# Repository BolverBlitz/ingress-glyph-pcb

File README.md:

# Ingress Glyph PCB firmware

Ingress Glyph PCB firmware for controlling LED chains and managing device features.

## Hardware revisions

- Rev 1 drives the LED chain from GPIO2 and has a 4.5 W hardware limit.
- Rev 2 drives the LED chain from GPIO19 and uses GPIO5 (SDA) / GPIO6 (SCL)
  for two TMP117 temperature sensors. Its hardware limit is 8 W with dimming* applied as needed.
- Select the revision under **Settings → Hardware revision**. A revision change
  is saved and restarts the controller automatically.

*On Rev 2, the hotter TMP117 reading limits every LED mode. The configured power
is available up to 50 °C, then linearly derated to 0 W at 70 °C. The LEDs remain
off if either sensor is missing or has not produced a valid reading for five
seconds.

## Buttons

- Button 1: GPIO1, active-low with internal pull-up.
- Button 2: GPIO4, active-low with internal pull-up.
- Double-press Button 1: cycle Glyph Sequence, Random Glyphs, and Draw. The new
  mode is saved after 10 seconds without further button input.
- Hold Button 1 for 2 seconds: toggle Flashlight mode on or off.
- In Flashlight mode, press Button 2: cycle 25%, 60%, and 100% brightness.
- Hold Button 2 on two nearby devices until the shared five-second rainbow
  finishes: add each other as friends and exchange the Draw page whose name
  exactly matches each Agent username. Connection setup happens before the
  rainbow starts, so total button-hold time can be longer than five seconds.
- On the Nearby page, send a Friendship Request instead. Requests expire after
  five minutes; the other board can accept while nearby, after which both boards
  run the normal five-second rainbow pairing animation. Pending requests can be
  cancelled and existing friends can be removed. Friendship is checked once when
  a new visit is recorded, regardless of Friend Mode. Removing a friend on one
  board notifies the other board immediately when nearby; if it is offline, the
  removal is reconciled at the next recorded visit. A nearby entry expires after 10 minutes without seeing the board,
  allowing a later visit to rediscover the board. Requests and nearby state
  are volatile and bounded to 32 entries; an unavailable board or older firmware
  does not delete a friend record. Physical Button 2 pairing remains supported.
- Hold both buttons for 10 seconds: enter Emergency mode, pulse white SOS, and
  broadcast the Emergency message to nearby devices.
- In Emergency mode, hold both buttons for 2 seconds: disable Emergency mode.

## Encounter history

Encounter history records `FIRST`/`LAST` pairs with UTC timestamps. Before NTP or
Browser Sync changes the clock, active encounters are closed on the old timeline
using elapsed uptime, then reopened on the corrected timeline. A 17-minute visit
therefore retains 17 minutes even if UTC jumps forward or backward. Time spent
nearby before the first usable UTC synchronization is recovered from uptime.
Clock corrections do not trigger extra friendship checks.

After reboot, the clock is restored to at least the newest saved encounter
timestamp or UTC checkpoint. An interrupted encounter without a `LAST` is
estimated from the next `FIRST`, capped at ten minutes; if that timestamp is
equal or earlier, the ten-minute fallback is used. These reboot estimates cannot
recover the actual encounter duration or time spent powered off. NTP and Browser
Sync can still correct an inaccurate clock backward. The normal encounter end
includes the existing ten-minute absence timeout.

## Coordinated friendship animation

Both devices need this firmware for the new friendship protocol. Discovery,
Emergency broadcasts and public identity reads still work with older firmware;
friend pairing does not fall back to the old animation timing.

The device with the smaller device ID opens a single BLE connection. It sends
an offer containing a random session ID and its identity. The other device
accepts only while Button 2 is held, at close range, and with no active emergency
or other session. Both identities are frozen for the exchange. After READY, the
coordinator measures the peer's `millis()` offset with three GATT reads and uses
the sample with the shortest round-trip time. Samples over 200 ms are rejected.
An acknowledged start is normally scheduled 350 ms ahead, in each device's own
clock. Slower links automatically receive up to 700 ms to complete the START
write/read acknowledgement. Rainbow progress and the success animation use this scheduled timeline,
including when the main loop delivers a frame slightly late.

Early release, emergency, an eight-second preparation timeout or 1.2 seconds
without peer contact cancel the session. Setup failures before the animation
starts retry automatically after 250 ms, with at most three attempts in an
eight-second window. Release and press again after an animation is cancelled
or the retry budget is exhausted. The incoming offer supplies the coordinator's
intent even if its request advertisement has not arrived; local button consent,
device-ID ordering, freshness and the RSSI threshold are still required.
Heartbeats continue through the hold; the completed status remains available
for six seconds so the peer can finish its acknowledgement. A new gesture after
the success animation can replace that retained status immediately; it does not
wait for the six-second cleanup or become blocked by it. Wireless cancellation
is best effort: loss of contact right at the completion boundary can still leave
only one device with a saved friendship. There is no atomic distributed commit.

All outgoing BLE connects, discovery and identity reads run in one FreeRTOS
worker. Queues transfer snapshots to the main task, which owns LED rendering,
settings and proximity storage. Disabling BLE invalidates pending work and
defers NimBLE destruction until the worker is finished. The HTTP Wi-Fi scan
returns a retryable error during pairing because its synchronous scan would
otherwise stall animation and temperature sampling.

The GATT status and command characteristics use UUID suffixes `03` and `04` in
the existing `44424700-696e-6772-6573-732d676c7970` service. Packets start with
`FP`, version 1 and a phase/command byte, followed by a little-endian 32-bit
session ID, the sender's six-byte device ID and a little-endian timestamp.
OFFER adds a glyph-present byte, a name-length byte, 64 name bytes and 69 RGBW
pixels. Other commands are START, CANCEL and HEARTBEAT. Status phases are IDLE,
READY and SCHEDULED; status reads stamp the server's current `millis()`.

Run `python -m unittest discover -s tests -v` for host checks of the timing,
release/timeout rules and malformed or stale packets.

## Build and flash

Install Python, then install/update PlatformIO and the project dependencies
from the repository root. Updating dependencies avoids silently retaining an
older cached ESP32 platform than release CI uses:

```powershell
python -m pip install --upgrade platformio
python -m platformio pkg update
python -m platformio run
python -m platformio run -e esp32-c3-devkitm-1-en --target upload --upload-port COM11
```

Open the serial monitor with:

```powershell
python -m platformio device monitor --port COM6 --baud 115200
```

At 115200 baud, the serial configuration console accepts:

```text
show
ip
rev 2
faction enlightened
wifi 1 "Network name" "Network password"
wifi 2 "Backup network" "Network password"
wifi-clear 1
```

Passwords are never printed by `show`. An empty password configures an open
network. Revision, faction and Wi-Fi changes are saved and restart the controller.
Use `faction res` / `faction resistance` for Resistance (blue), or
`faction enl` / `faction enlightened` for Enlightened (green). Faction names
and aliases are case-insensitive. The `show` command includes the saved faction.

To display the IP addresses of all controllers connected over USB serial, run:

```powershell
python scripts/find_device_ips.py
```

Specific ports can be supplied when other serial equipment is connected:

```powershell
python scripts/find_device_ips.py COM11 COM12
```

The default build produces three independent firmware images: English (`en`),
German (`de`), and Japanese (`ja`). Each image contains only its own UI language;
language is selected when flashing, not in Settings. The build automatically
translates and minifies `WebUI/` into a `localized_web_ui.h` header inside each
PlatformIO build directory. For example, the English OTA
image is `.pio/build/esp32-c3-devkitm-1-en/firmware.bin`. Use `-e
esp32-c3-devkitm-1-de` or `-e esp32-c3-devkitm-1-ja` to flash another language.

Keep WebUI JavaScript readable, with indented functions and comments. The Python
pre-build script translates the sources, minifies HTML, JavaScript and CSS, and
gzip-compresses all static assets before embedding them in firmware. Assets
are served directly from flash with `Content-Encoding: gzip`; decompression
happens in the browser. Each build reports the raw, minified and compressed
payload sizes. It compares standard gzip with Zopfli and keeps the smaller
stream. The script uses the pinned `minify-html` and `zopfli`
dependencies from `scripts/requirements-web-ui.txt`, automatically installed into
`.pio/web-ui-deps` on the first build if needed. This first build requires
internet access; later builds reuse the dependency. Node.js is not needed to
build or flash. Generated files do not overwrite the sources in `WebUI/`.

Run the minification regression checks with `python -m unittest discover -s
tests -v`. If Node.js is installed, they also check JavaScript behavior and
syntax for all three languages; otherwise those checks are skipped.

Link-time optimization reduces firmware size. A final binary-size check rejects
images that exceed the OTA slot, including image headers and alignment padding.

LED frames use a fixed GRBW buffer and the SK6812 RMT driver directly, avoiding
a second LED transport backend and its firmware overhead.

JSON stores 32-bit integers and floats for IDs, UTC timestamps, settings and
sensor readings, without ArduinoJson's 64-bit extension pool. The accumulated
encounter-time counter retains its full 64-bit decimal output through an
explicit raw-number writer. Tests cover its maximum value, unsigned IDs and
timestamps beyond 2038.

`src/firmware_build_config.h` disables Arduino's unused Espressif network
provisioning event integration. Wi-Fi credentials are configured through this
project's captive portal or serial console. This lets the linker discard the
provisioning manager, protobuf and provisioning security code. Using Arduino's
`WiFiProv` feature in future requires restoring this configuration option.

UTC synchronization uses the thread-safe SNTP API directly, avoiding the
unused POSIX timezone parser. Formatting uses the vendored nanoprintf C11
formatter, including floats and 64-bit integers, through linker wrappers
for the standard printf family. Its upstream revision and license are recorded
in `lib/nanoprintf/`. Release builds retain the fixed-decimal float formats used
by firmware diagnostics; debug builds also enable scientific/general/hex float
formats.

Release builds omit automatic flash core dumps and the full SDK error-name
catalogue. Serial panic reporting and reboot remain enabled. Common errors
retain their names; other errors use `ESP_ERR_UNKNOWN`, with numeric codes in
SDK diagnostics and in `esp_err_to_name_r()` output. Debug builds retain the
full SDK diagnostics. Release assertions still evaluate and abort on failure,
but omit their file/function/expression text, and internal NimBLE host logging
is disabled. Application logs remain available. The partition layout and stored
application data are unchanged by these optimizations.

The source build disables C++ exceptions and unwind-table generation because
the application and its source dependencies use explicit error returns. Unwind
tables in the precompiled ESP-IDF/C++ libraries are retained. New dependencies
that require exceptions need these build flags reviewed.

NimBLE Security Manager (legacy pairing and Secure Connections), bonding, and
bond persistence are disabled through the library's `MYNEWT_VAL_*` overrides.
BLE discovery and public username/glyph reads remain available. Button-based
friend pairing stores an application friend record, independently of BLE bonds.
Private or authenticated BLE features would require restoring security support.

The GATT configuration retains service/characteristic discovery and individual
short/long reads and writes used by friendship exchanges. Unused batch reads,
included-service discovery, reliable multi-attribute writes and multi-handle
notifications are compiled out.

For an interactive build, flash, hardware-revision setup, and optional Wi-Fi
setup, run one of the helper scripts from the repository root:

```powershell
.\flash.ps1
```

```bash
bash ./flash.sh
```

When Wi-Fi setup is requested, the script waits
for the connection and prints the controller's assigned IP address.
On Windows, the port prompt accepts either `COM11` or just `11`.
Both flash helpers prompt for a faction: `res` / `resistance` (blue) or
`enl` / `enlightened` (green). Leave it blank to keep the board's current faction. On Windows, you
can also supply it directly:

```powershell
.\flash.ps1 -Port COM12 -Revision 2 -Language en -Faction enl
```

Serial configuration waits up to 60 seconds for the controller to answer a
`show` query before sending settings, and again after each saved change restarts
the board. Saved Wi-Fi profiles can delay startup while connection attempts
finish. If flashing succeeded but configuration failed, retry configuration
without rebuilding or uploading:

```powershell
python scripts/configure_serial.py --port COM11 --revision 2 --faction enl
```

### Backup and restore (Windows)

Close serial monitors, then save a complete snapshot of a board:

```powershell
.\backup.ps1 -Port COM12
.\backup.ps1 -Port COM12 -Output .\backups\my-board.zip
```

Without `-Output`, a unique timestamped ZIP is saved in `backups/`. Existing
backup files are never overwritten. The snapshot includes the entire 4 MB
flash: firmware and UI language, partition table, NVS, settings, Wi-Fi,
faction, drawings, friends, history, clock checkpoints, and backup files on
the board. Reading flash temporarily stops the firmware and restarts the board
afterward. These scripts use the ESP32 tools installed by PlatformIO; run a
firmware build once if the tools are not installed yet.

To put that board back exactly as it was at backup time:

```powershell
.\restore.ps1 -Port COM12 -Backup .\backups\my-board.zip
```

Restore validates the archive format, chip type, image size, and SHA-256 checksum
before accessing the board. It then replaces all flash, verifies the written
image, and restarts the board. This also restores the backed-up firmware;
changes made after the backup are replaced. Use these images with the original
ESP32-C3 4 MB board. Hardware MAC addresses and eFuses are not backed up or changed.
If a restore is interrupted, rerun it with the same backup.

Backups contain Wi-Fi passwords and personal history. Keep them private;
the default `backups/` directory is ignored by Git. No board is erased merely
by creating a backup.

The same operations are available from Python on other platforms:

```bash
python scripts/board_backup.py backup --port /dev/ttyUSB0 --output backups/my-board.zip
python scripts/board_backup.py restore --port /dev/ttyUSB0 --backup backups/my-board.zip
```

### Factory reset (Windows)

To remove all saved board data and reinstall firmware with factory defaults:

```powershell
.\factory-reset.ps1 -Port COM12
```

Use `-Language de` or `-Language ja` for German or Japanese (default: English).
The script asks for hardware revision **1** or **2** before building, then saves
your selection after flashing. Use `-Revision 2` to supply it directly.
Close serial monitors before running. The script builds first, then erases the
entire flash and uploads fresh firmware. This permanently removes settings,
Wi-Fi credentials, drawings, display preferences, friends, encounter history,
clock checkpoints, backup files, and ESP32 NVS data. No previous configuration
is restored; only the selected hardware revision is configured afterward.
The board's hardware MAC address remains unchanged.

If upload fails after erasing, rerun the script to restore the firmware.

## Display effects

The Main page's Effects section is available in Glyph Sequence, Random Glyphs,
and Draw modes. Choose Off or Fade. Fade also applies to friend glyph playback
when enabled, with six moving directions, a Global fade, and three transition types:

- Quickfade: each LED reaches black before fading into the next frame, while
  outgoing and incoming waves overlap across the display.
- Slowfade: the entire display reaches black before the incoming wave starts.
- Mix: directly blend the old and new frames without inserting a black step.

Global fades all LEDs together without a moving wave.
Fade duration (100–60000 ms) covers the entire transition. The switch interval
is the hold time after the transition finishes. Effects support live preview and
are stored with the display settings when saved. Existing settings default to
Off. Flashlight, SOS, and pairing feedback retain their immediate controls.

## Releases

Push a semantic-version tag matching `FIRMWARE_VERSION` in `src/config.h` to
build and publish a GitHub release automatically. For example:

```bash
git tag v0.9.8
git push origin v0.9.8
```

The release contains an OTA-ready binary and SHA-256 checksum for each language,
named `ingress-glyph-pcb-vX.Y.Z-en.bin`, `-de.bin`, and `-ja.bin`. The Settings
page offers the download matching the language currently installed.
Once the repository is public, the Settings page checks the latest release once
when it loads. Network and GitHub errors are ignored so hotspot mode continues
to work normally.

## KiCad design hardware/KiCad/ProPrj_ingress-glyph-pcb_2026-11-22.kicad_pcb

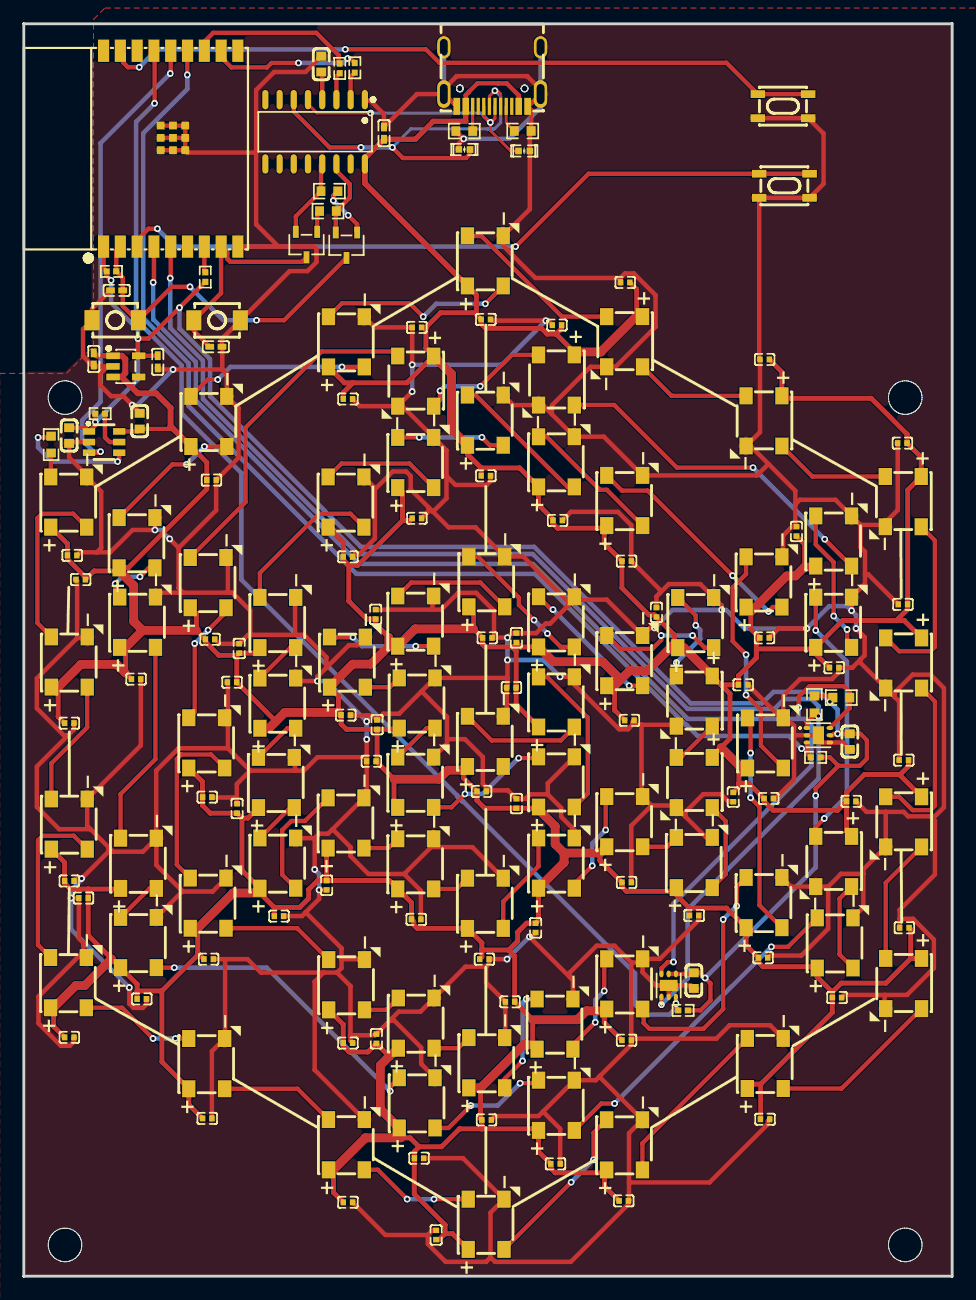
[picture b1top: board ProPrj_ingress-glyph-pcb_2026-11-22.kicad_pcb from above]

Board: 2 copper layers, 82.9 x 111.9 mm, 177 parts (0 on the bottom side), 97 nets.

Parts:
BOOT: SW-SMD_L4.0-W3.0-LS4.8
C1, C2, C7, C149, C150: C0603
C3, C4, C9: C0402_NEW
C5, C6, C11, C12, C13, C14, C15, C16, C17, C18, C19, C20, C21, C22, C23, C24, C25, C26, C27, C28, C29, C30, C31, C32, C33, C34, C35, C36, C37, C38, C39, C40, C41, C42, C43, C44, C45, C46, C47, C48, C49, C50, C51, C52, C53, C54, C55, C56, C57, C58, C59, C60, C61, C62, C63, C64, C65, C66, C67, C68, C69, C70, C71, C72, C73, C74, C75, C76, C77, C78, C79: C0402
D1, D2: D0402-BI
EN: SW-SMD_L4.0-W3.0-LS4.8
LED1, LED2, LED3, LED4, LED5, LED6, LED7, LED8, LED9, LED10, LED11, LED12, LED13, LED14, LED15, LED16, LED17, LED18, LED19, LED20, LED21, LED22, LED23, LED24, LED25, LED26, LED27, LED28, LED29, LED30, LED31, LED32, LED33, LED34, LED35, LED36, LED37, LED38, LED39, LED40, LED41, LED42, LED43, LED44, LED45, LED46, LED47, LED48, LED49, LED50, LED51, LED52, LED53, LED54, LED55, LED56, LED57, LED58, LED59, LED60, LED61, LED62, LED63, LED64, LED65, LED66, LED67, LED68, LED69: LED-SMD_4P-L5.0-W4.9-BR
Q3, Q4: SOT-23-3_L2.9-W1.4-P1.91-LS2.6-BR
R1, R2, R7, R8, R11, R107, R108: R0603
R3, R4, R5, R6, R9, R10, R174: R0402
SW1, SW2: SW-SMD_4P-L4.2-W3.3-P2.15-LS5.1
U1: BULETM-SMD_ESPRESSIF_ESP32-C3-WROOM-02-N4-4MB
U2: SOP-16_L10.0-W3.9-P1.27-LS6.0-BL
U3: USB-C-SMD_BX-TYPE-C-C-MWT16P
U4, U5: WSON-6_L2.0-W2.0-P0.65-TL-EP
U32: SOT-23-5_L3.0-W1.6-P0.95-LS2.8-BR
U125: SOT-23-6_L2.9-W1.6-P0.95-LS2.8-BR

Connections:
3.3V: C1.1, C6.2, C7.1, C149.1, R3.2, R4.2, R9.2, R10.2, R107.2, R108.2, R174.1, U1.1, U4.5, U5.4, U5.5, U32.5, U125.1
$1N5: LED1.4, LED2.2
$1N6: LED2.4, LED3.2
$1N8: LED3.4, LED4.2
$1N10: LED4.4, LED5.2
$1N12: LED5.4, LED6.2
$1N14: LED6.4, LED7.2
$1N16: LED7.4, LED8.2
$1N18: LED8.4, LED9.2
$1N21: LED16.4, LED17.2
$1N22: LED10.4, LED11.2
$1N23: LED15.4, LED16.2
$1N24: LED11.4, LED12.2
$1N25: LED17.4, LED18.2
$1N26: LED12.4, LED13.2
$1N27: LED14.4, LED15.2
$1N28: LED13.4, LED14.2
$1N40: LED34.4, LED35.2
$1N41: LED19.4, LED20.2
$1N42: LED25.4, LED26.2
$1N43: LED31.4, LED32.2
$1N44: LED30.4, LED31.2
$1N45: LED33.4, LED34.2
$1N46: LED21.4, LED22.2
$1N47: LED23.4, LED24.2
$1N48: LED28.4, LED29.2
$1N49: LED32.4, LED33.2
$1N50: LED20.4, LED21.2
$1N51: LED35.4, LED36.2
$1N52: LED26.4, LED27.2
$1N53: LED22.4, LED23.2
$1N54: LED29.4, LED30.2
$1N55: LED24.4, LED25.2
$1N79: LED37.4, LED38.2
$1N80: LED43.4, LED44.2
$1N81: LED52.4, LED53.2
$1N82: LED61.4, LED62.2
$1N83: LED53.4, LED54.2
$1N84: LED64.4, LED65.2
$1N85: LED49.4, LED50.2
$1N86: LED51.4, LED52.2
$1N87: LED42.4, LED43.2
$1N88: LED48.4, LED49.2
$1N89: LED50.4, LED51.2
$1N91: LED58.4, LED59.2
$1N92: LED66.4, LED67.2
$1N93: LED55.4, LED56.2
$1N94: LED60.4, LED61.2
$1N95: LED38.4, LED39.2
$1N96: LED44.4, LED45.2
$1N97: LED39.4, LED40.2
$1N98: LED67.4, LED68.2
$1N99: LED40.4, LED41.2
$1N100: LED68.4, LED69.2
$1N101: LED41.4, LED42.2
$1N102: LED56.4, LED57.2
$1N103: LED62.4, LED63.2
$1N105: LED65.4, LED66.2
$1N106: LED59.4, LED60.2
$1N107: LED57.4, LED58.2
$1N108: LED46.4, LED47.2
$1N109: LED47.4, LED48.2
$1N156: LED1.2, R11.1
$6N885: R8.1, U3.A5
$6N893: R7.2, U3.B5
$6N1473: C2.1, U2.4
$6N1474: R5.2, U2.2
$6N1482: Q4.1, R2.1
$6N1484: Q3.1, R1.2
$6N6405: R6.2, U2.3
$6N7331: R3.1, U1.7
$6N7359: R174.2, U125.5
+5V: C3.1, C5.2, C11.1, C12.1, C13.1, C14.1, C15.1, C16.1, C17.1, C18.1, C19.1, C20.1, C21.1, C22.1, C23.1, C24.1, C25.1, C26.1, C27.1, C28.1, C29.1, C30.1, C31.1, C32.1, C33.1, C34.1, C35.1, C36.1, C37.1, C38.1, C39.1, C40.1, C41.1, C42.1, C43.1, C44.1, C45.1, C46.1, C47.1, C48.1, C49.1, C50.1, C51.1, C52.1, C53.1, C54.1, C55.1, C56.1, C57.1, C58.1, C59.1, C60.1, C61.1, C62.1, C63.1, C64.1, C65.1, C66.1, C67.1, C68.1, C69.1, C70.1, C71.1, C72.1, C73.1, C74.1, C75.1, C76.1, C77.1, C78.1, C79.1, C150.1, LED1.3, LED2.3, LED3.3, LED4.3, LED5.3, LED6.3, LED7.3, LED8.3, LED9.3, LED10.3, LED11.3, LED12.3, LED13.3, LED14.3, LED15.3, LED16.3, LED17.3, LED18.3, LED19.3, LED20.3, LED21.3, LED22.3, LED23.3, LED24.3, LED25.3, LED26.3, LED27.3, LED28.3, LED29.3, LED30.3, LED31.3, LED32.3, LED33.3, LED34.3, LED35.3, LED36.3, LED37.3, LED38.3, LED39.3, LED40.3, LED41.3, LED42.3, LED43.3, LED44.3, LED45.3, LED46.3, LED47.3, LED48.3, LED49.3, LED50.3, LED51.3, LED52.3, LED53.3, LED54.3, LED55.3, LED56.3, LED57.3, LED58.3, LED59.3, LED60.3, LED61.3, LED62.3, LED63.3, LED64.3, LED65.3, LED66.3, LED67.3, LED68.3, LED69.3, U2.16, U3.A4B9, U3.B4A9, U32.1, U32.3, U125.6
ALT1: R9.1, U1.13, U4.3
ALT2: R10.1, U1.15, U5.3
BUTTON1: SW1.1, SW1.2, U1.3
BUTTON2: SW2.1, SW2.2, U1.17
D+: D1.2, U2.5, U3.A6, U3.B6
D-: D2.2, U2.6, U3.A7, U3.B7
DIO: BOOT.2, C4.2, Q3.3, U1.8
DTR: Q3.2, R2.2, U2.13
EN: C9.2, EN.2, Q4.3, R4.1, U1.2
GND: BOOT.1, C1.2, C2.2, C3.2, C4.1, C5.1, C6.1, C7.2, C9.1, C11.2, C12.2, C13.2, C14.2, C15.2, C16.2, C17.2, C18.2, C19.2, C20.2, C21.2, C22.2, C23.2, C24.2, C25.2, C26.2, C27.2, C28.2, C29.2, C30.2, C31.2, C32.2, C33.2, C34.2, C35.2, C36.2, C37.2, C38.2, C39.2, C40.2, C41.2, C42.2, C43.2, C44.2, C45.2, C46.2, C47.2, C48.2, C49.2, C50.2, C51.2, C52.2, C53.2, C54.2, C55.2, C56.2, C57.2, C58.2, C59.2, C60.2, C61.2, C62.2, C63.2, C64.2, C65.2, C66.2, C67.2, C68.2, C69.2, C70.2, C71.2, C72.2, C73.2, C74.2, C75.2, C76.2, C77.2, C78.2, C79.2, C149.2, C150.2, D1.1, D2.1, EN.1, LED1.1, LED2.1, LED3.1, LED4.1, LED5.1, LED6.1, LED7.1, LED8.1, LED9.1, LED10.1, LED11.1, LED12.1, LED13.1, LED14.1, LED15.1, LED16.1, LED17.1, LED18.1, LED19.1, LED20.1, LED21.1, LED22.1, LED23.1, LED24.1, LED25.1, LED26.1, LED27.1, LED28.1, LED29.1, LED30.1, LED31.1, LED32.1, LED33.1, LED34.1, LED35.1, LED36.1, LED37.1, LED38.1, LED39.1, LED40.1, LED41.1, LED42.1, LED43.1, LED44.1, LED45.1, LED46.1, LED47.1, LED48.1, LED49.1, LED50.1, LED51.1, LED52.1, LED53.1, LED54.1, LED55.1, LED56.1, LED57.1, LED58.1, LED59.1, LED60.1, LED61.1, LED62.1, LED63.1, LED64.1, LED65.1, LED66.1, LED67.1, LED68.1, LED69.1, R7.1, R8.2, SW1.3, SW1.4, SW2.3, SW2.4, U1.9, U1.19, U2.1, U3.1, U3.2, U3.3, U3.4, U3.A1B12, U3.B1A12, U4.2, U4.4, U4.7, U5.2, U5.7, U32.2, U125.2
LED_PIN: R11.2, U125.4
LED_PIN_3V3: U1.14, U125.3
LED_ROW1: LED9.4, LED10.2
LED_ROW2: LED18.4, LED19.2
LED_ROW3: LED27.4, LED28.2
LED_ROW4: LED36.4, LED37.2
LED_ROW5: LED45.4, LED46.2
LED_ROW6: LED54.4, LED55.2
LED_ROW7: LED63.4, LED64.2
RTS: Q4.2, R1.1, U2.14
RXD: R5.1, U1.11
SCL: R108.1, U1.5, U4.1, U5.1
SDA: R107.1, U1.4, U4.6, U5.6
TXD: R6.1, U1.12
